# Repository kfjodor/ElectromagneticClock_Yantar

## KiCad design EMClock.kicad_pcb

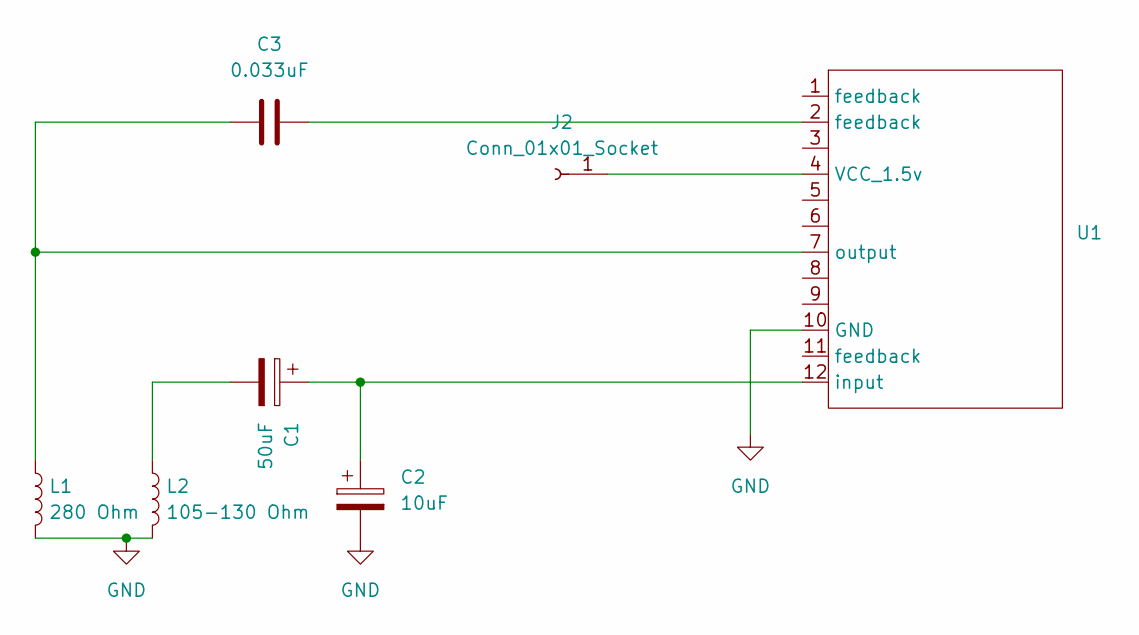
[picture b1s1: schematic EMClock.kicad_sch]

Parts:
C1: 50uF; CP_Radial_D5.0mm_P2.00mm
C2: 10uF; CP_Radial_Tantal_D5.0mm_P2.50mm
C3: 0.033uF; C_0603_1608Metric_Pad1.08x0.95mm_HandSolder
J2: Conn_01x01_Socket; PinHeader_1x01_P2.54mm_Vertical
L1: 280 Ohm; C_0603_1608Metric
L2: 105-130 Ohm; C_0603_1608Metric
U1: K264GF1

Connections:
GND: C2.2, L1.2, L2.2, U1.10 (GND)
unnamed: C1.2, L2.1
unnamed: C3.1, U1.2 (feedback)
unnamed: J2.1, U1.4 (VCC_1.5v)
unnamed: C1.1, C2.1, U1.12 (input)
unnamed: C3.2, L1.1, U1.7 (output)

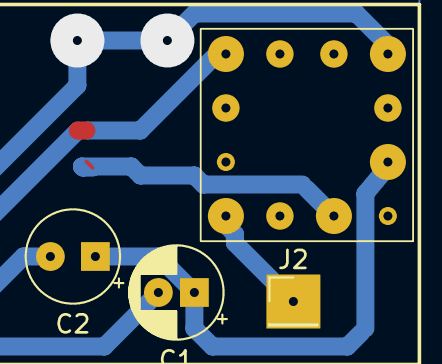
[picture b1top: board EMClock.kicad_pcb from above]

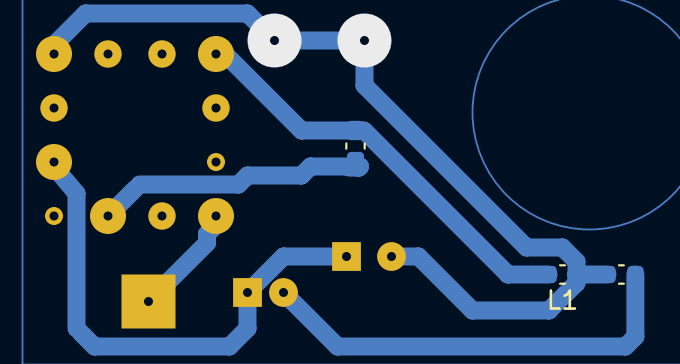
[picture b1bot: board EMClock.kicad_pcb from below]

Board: 2 copper layers, 7 parts (3 on the bottom side), 6 nets.

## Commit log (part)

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2026-03-26 initial
2026-03-27 coil data
